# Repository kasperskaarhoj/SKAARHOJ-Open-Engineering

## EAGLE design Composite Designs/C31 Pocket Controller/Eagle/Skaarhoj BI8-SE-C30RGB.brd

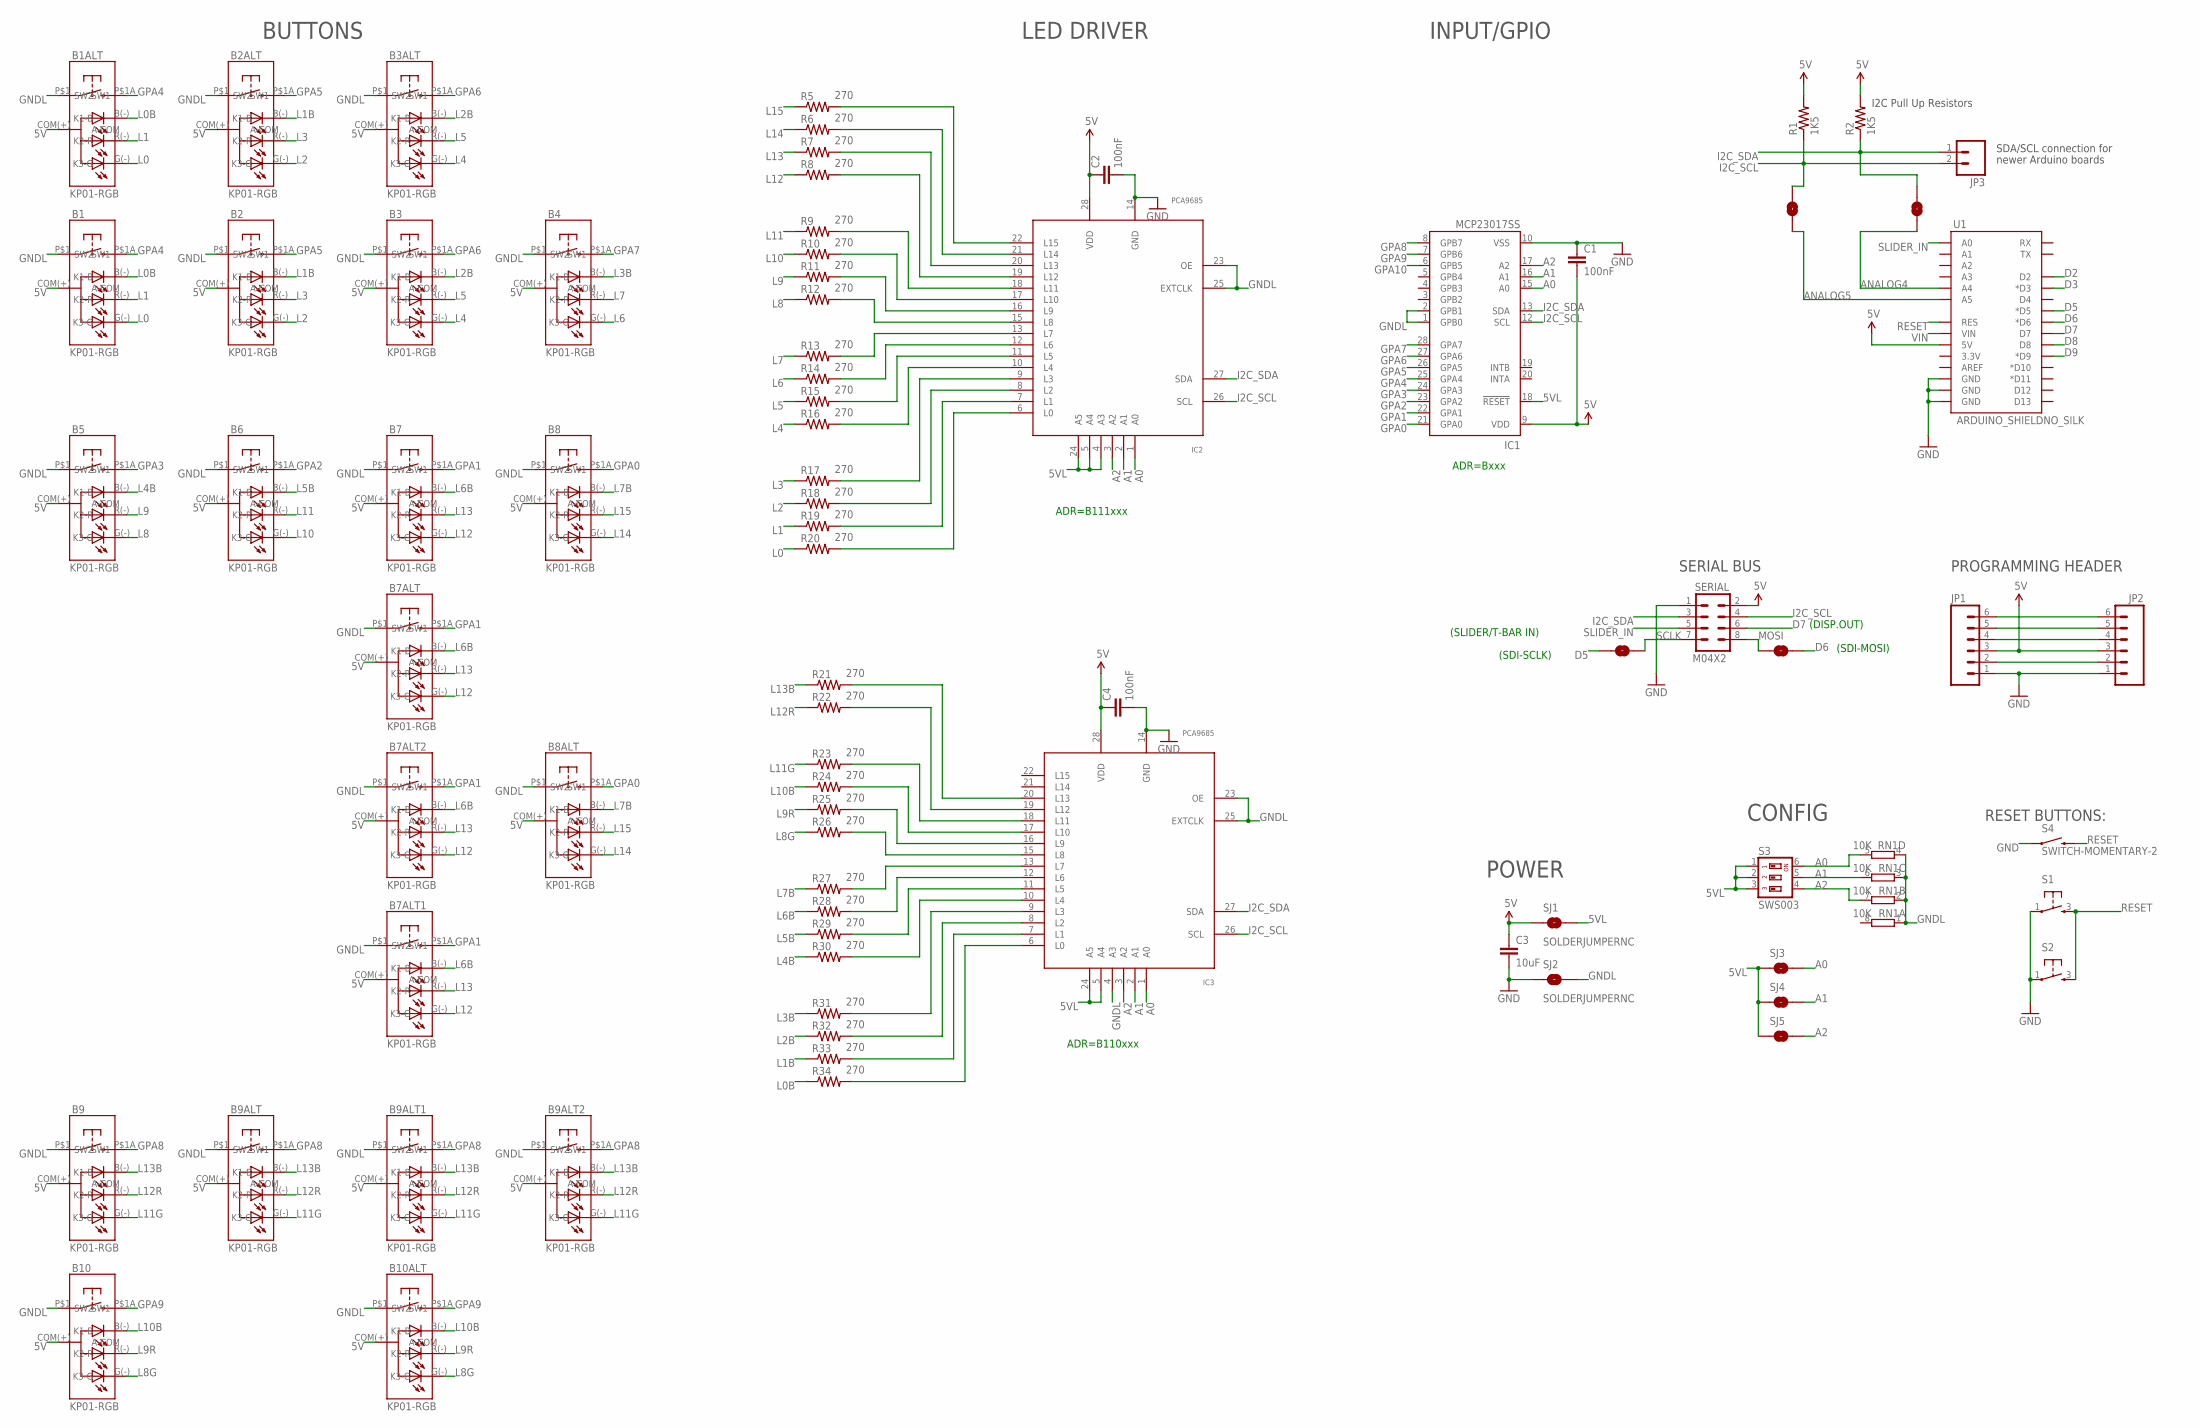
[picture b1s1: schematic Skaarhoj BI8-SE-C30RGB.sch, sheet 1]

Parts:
B1, B1ALT, B2, B2ALT, B3, B3ALT, B4, B5, B7, B8, B9, B10: KP01-RGB; NKK-KP01
B6, B7ALT, B7ALT1, B7ALT2, B8ALT, B9ALT, B9ALT1, B9ALT2, B10ALT: KP01-RGB; NKK-KP01_LESSHOLES
C1, C2, C4: 100nF; 0603-CAP
C3: 10uF; 0805
IC1: MCP23017SS; SSOP28; MPN MCP23017-E/SS
IC2, IC3: PCA9685; TSSOP28
JP1, JP2: M06POLAR; MOLEX-1X6
JP3: M02PTH; 1X02
MOSI->D6: SOLDERJUMPERNC; SJ_2S
R1, R2: 1K5; 0603-RES
R5, R6, R7, R8, R9, R10, R11, R12, R13, R14, R15, R16, R17, R18, R19, R20, R21, R22, R23, R24, R25, R26, R27, R28, R29, R30, R31, R32, R33, R34: 270; 0603-RES
RN1: 10K; CAY16_HAND
S1, S2: TAC_SWITCH; PUSHBUTTON
S3: SWS003; SMS-003
S3->A2, S3->A3: SOLDERJUMPERNC; SJ_2S
S4: SWITCH-MOMENTARY-2; TACTILE_SWITCH_TALL
SCLK->D5: SOLDERJUMPERNC; SJ_2S
SERIAL: M04X2; 2X4
SJ1, SJ2, SJ3, SJ4, SJ5: SOLDERJUMPERNC; SJ_2S
U1: ARDUINO_SHIELDNO_SILK; DUEMILANOVE_VIAS

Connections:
5V: B1.COM(+) (A-COM), B1ALT.COM(+) (A-COM), B2.COM(+) (A-COM), B2ALT.COM(+) (A-COM), B3.COM(+) (A-COM), B3ALT.COM(+) (A-COM), B4.COM(+) (A-COM), B5.COM(+) (A-COM), B6.COM(+) (A-COM), B7.COM(+) (A-COM), B7ALT.COM(+) (A-COM), B7ALT1.COM(+) (A-COM), B7ALT2.COM(+) (A-COM), B8.COM(+) (A-COM), B8ALT.COM(+) (A-COM), B9.COM(+) (A-COM), B9ALT.COM(+) (A-COM), B9ALT1.COM(+) (A-COM), B9ALT2.COM(+) (A-COM), B10.COM(+) (A-COM), B10ALT.COM(+) (A-COM), C1.2, C2.1, C3.1, C4.1, IC1.9 (VDD), IC2.28 (VDD), IC3.28 (VDD), JP1.3, JP2.3, R1.2, R2.2, SERIAL.2, SJ1.1, U1.5V
5VL: IC1.18 (!RESET), IC2.4 (A3), IC2.5 (A4), IC2.24 (A5), IC3.5 (A4), IC3.24 (A5), S3.1, S3.2, S3.3, SJ1.2, SJ3.1, SJ4.1, SJ5.1
A0: IC1.15 (A0), IC2.1 (A0), IC3.1 (A0), RN1.5 (2), S3.6, SJ3.2
A1: IC1.16 (A1), IC2.2 (A1), IC3.2 (A1), RN1.6 (2), S3.5, SJ4.2
A2: IC1.17 (A2), IC2.3 (A2), IC3.3 (A2), RN1.7 (2), S3.4, SJ5.2
ANALOG4: S3->A3.2, U1.A4
ANALOG5: S3->A2.2, U1.A5
D2: U1.D2
D3: U1.D3 (*D3)
D5: SCLK->D5.1, U1.D5 (*D5)
D6: MOSI->D6.2, U1.D6 (*D6)
D7: SERIAL.6, U1.D7
D8: U1.D8
D9: U1.D9 (*D9)
GND: C1.1, C2.2, C3.2, C4.2, IC1.10 (VSS), IC2.14 (GND), IC3.14 (GND), JP1.1, JP2.1, S1.1, S2.1, S4.A2 (1), SERIAL.1, SJ2.1, U1.GND@0 (GND), U1.GND@1 (GND), U1.GND@2 (GND)
GNDL: B1.P$1 (SW1), B1ALT.P$1 (SW1), B2.P$1 (SW1), B2ALT.P$1 (SW1), B3.P$1 (SW1), B3ALT.P$1 (SW1), B4.P$1 (SW1), B5.P$1 (SW1), B6.P$1 (SW1), B7.P$1 (SW1), B7ALT.P$1 (SW1), B7ALT1.P$1 (SW1), B7ALT2.P$1 (SW1), B8.P$1 (SW1), B8ALT.P$1 (SW1), B9.P$1 (SW1), B9ALT.P$1 (SW1), B9ALT1.P$1 (SW1), B9ALT2.P$1 (SW1), B10.P$1 (SW1), B10ALT.P$1 (SW1), IC1.1 (GPB0), IC1.2 (GPB1), IC2.23 (OE), IC2.25 (EXTCLK), IC3.4 (A3), IC3.23 (OE), IC3.25 (EXTCLK), RN1.1, RN1.2 (1), RN1.3 (1), RN1.4 (1), SJ2.2
GPA0: B8.P$1A (SW2), B8ALT.P$1A (SW2), IC1.21 (GPA0)
GPA1: B7.P$1A (SW2), B7ALT.P$1A (SW2), B7ALT1.P$1A (SW2), B7ALT2.P$1A (SW2), IC1.22 (GPA1)
GPA2: B6.P$1A (SW2), IC1.23 (GPA2)
GPA3: B5.P$1A (SW2), IC1.24 (GPA3)
GPA4: B1.P$1A (SW2), B1ALT.P$1A (SW2), IC1.25 (GPA4)
GPA5: B2.P$1A (SW2), B2ALT.P$1A (SW2), IC1.26 (GPA5)
GPA6: B3.P$1A (SW2), B3ALT.P$1A (SW2), IC1.27 (GPA6)
GPA7: B4.P$1A (SW2), IC1.28 (GPA7)
GPA8: B9.P$1A (SW2), B9ALT.P$1A (SW2), B9ALT1.P$1A (SW2), B9ALT2.P$1A (SW2), IC1.8 (GPB7)
GPA9: B10.P$1A (SW2), B10ALT.P$1A (SW2), IC1.7 (GPB6)
GPA10: IC1.6 (GPB5)
I2C_SCL: IC1.12 (SCL), IC2.26 (SCL), IC3.26 (SCL), JP3.2, R1.1, S3->A2.1, SERIAL.4
I2C_SDA: IC1.13 (SDA), IC2.27 (SDA), IC3.27 (SDA), JP3.1, R2.1, S3->A3.1, SERIAL.3
L0: B1.G(-) (K3-G), B1ALT.G(-) (K3-G), R20.1
L0B: B1.B(-) (K1-B), B1ALT.B(-) (K1-B), R34.1
L1: B1.R(-) (K2-R), B1ALT.R(-) (K2-R), R19.1
L1B: B2.B(-) (K1-B), B2ALT.B(-) (K1-B), R33.1
L2: B2.G(-) (K3-G), B2ALT.G(-) (K3-G), R18.1
L2B: B3.B(-) (K1-B), B3ALT.B(-) (K1-B), R32.1
L3: B2.R(-) (K2-R), B2ALT.R(-) (K2-R), R17.1
L3B: B4.B(-) (K1-B), R31.1
L4: B3.G(-) (K3-G), B3ALT.G(-) (K3-G), R16.1
L4B: B5.B(-) (K1-B), R30.1
L5: B3.R(-) (K2-R), B3ALT.R(-) (K2-R), R15.1
L5B: B6.B(-) (K1-B), R29.1
L6: B4.G(-) (K3-G), R14.1
L6B: B7.B(-) (K1-B), B7ALT.B(-) (K1-B), B7ALT1.B(-) (K1-B), B7ALT2.B(-) (K1-B), R28.1
L7: B4.R(-) (K2-R), R13.1
L7B: B8.B(-) (K1-B), B8ALT.B(-) (K1-B), R27.1
L8: B5.G(-) (K3-G), R12.1
L8G: B10.G(-) (K3-G), B10ALT.G(-) (K3-G), R26.1
L9: B5.R(-) (K2-R), R11.1
L9R: B10.R(-) (K2-R), B10ALT.R(-) (K2-R), R25.1
L10: B6.G(-) (K3-G), R10.1
L10B: B10.B(-) (K1-B), B10ALT.B(-) (K1-B), R24.1
L11: B6.R(-) (K2-R), R9.1
L11G: B9.G(-) (K3-G), B9ALT.G(-) (K3-G), B9ALT1.G(-) (K3-G), B9ALT2.G(-) (K3-G), R23.1
L12: B7.G(-) (K3-G), B7ALT.G(-) (K3-G), B7ALT1.G(-) (K3-G), B7ALT2.G(-) (K3-G), R8.1
L12R: B9.R(-) (K2-R), B9ALT.R(-) (K2-R), B9ALT1.R(-) (K2-R), B9ALT2.R(-) (K2-R), R22.1
L13: B7.R(-) (K2-R), B7ALT.R(-) (K2-R), B7ALT1.R(-) (K2-R), B7ALT2.R(-) (K2-R), R7.1
L13B: B9.B(-) (K1-B), B9ALT.B(-) (K1-B), B9ALT1.B(-) (K1-B), B9ALT2.B(-) (K1-B), R21.1
L14: B8.G(-) (K3-G), B8ALT.G(-) (K3-G), R6.1
L15: B8.R(-) (K2-R), B8ALT.R(-) (K2-R), R5.1
MOSI: MOSI->D6.1, SERIAL.8
unnamed: JP1.2, JP2.2
unnamed: IC3.13 (L7), R27.2
unnamed: IC3.12 (L6), R28.2
unnamed: IC2.13 (L7), R13.2
unnamed: IC2.12 (L6), R14.2
unnamed: IC3.11 (L5), R29.2
unnamed: IC2.11 (L5), R15.2
unnamed: IC2.10 (L4), R16.2
unnamed: IC2.9 (L3), R17.2
unnamed: IC2.8 (L2), R18.2
unnamed: IC2.7 (L1), R19.2
unnamed: IC3.10 (L4), R30.2
unnamed: IC3.9 (L3), R31.2
unnamed: IC3.8 (L2), R32.2
unnamed: IC3.7 (L1), R33.2
unnamed: IC3.6 (L0), R34.2
unnamed: IC3.15 (L8), R26.2
unnamed: IC2.6 (L0), R20.2
unnamed: IC2.15 (L8), R12.2
unnamed: IC2.16 (L9), R11.2
unnamed: IC2.17 (L10), R10.2
unnamed: IC2.18 (L11), R9.2
unnamed: IC2.19 (L12), R8.2
unnamed: IC2.20 (L13), R7.2
unnamed: IC2.21 (L14), R6.2
unnamed: IC2.22 (L15), R5.2
unnamed: IC3.16 (L9), R25.2
unnamed: IC3.17 (L10), R24.2
unnamed: IC3.18 (L11), R23.2
unnamed: IC3.19 (L12), R22.2
unnamed: IC3.20 (L13), R21.2
unnamed: JP1.4, JP2.4
unnamed: JP1.5, JP2.5
unnamed: JP1.6, JP2.6
RESET: S1.3, S2.3, S4.B2 (2), U1.RES
SCLK: SCLK->D5.2, SERIAL.7
SLIDER_IN: SERIAL.5, U1.A0
VIN: U1.VIN

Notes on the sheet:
PROGRAMMING HEADER
I2C Pull Up Resistors
SDA/SCL connection for
newer Arduino boards
SERIAL BUS
(SLIDER/T-BAR IN)
(SDI-SCLK)
(SDI-MOSI)
(DISP.OUT)
RESET BUTTONS:
ADR=B111xxx
ADR=Bxxx
BUTTONS
LED DRIVER
INPUT/GPIO
POWER
CONFIG
ADR=B110xxx

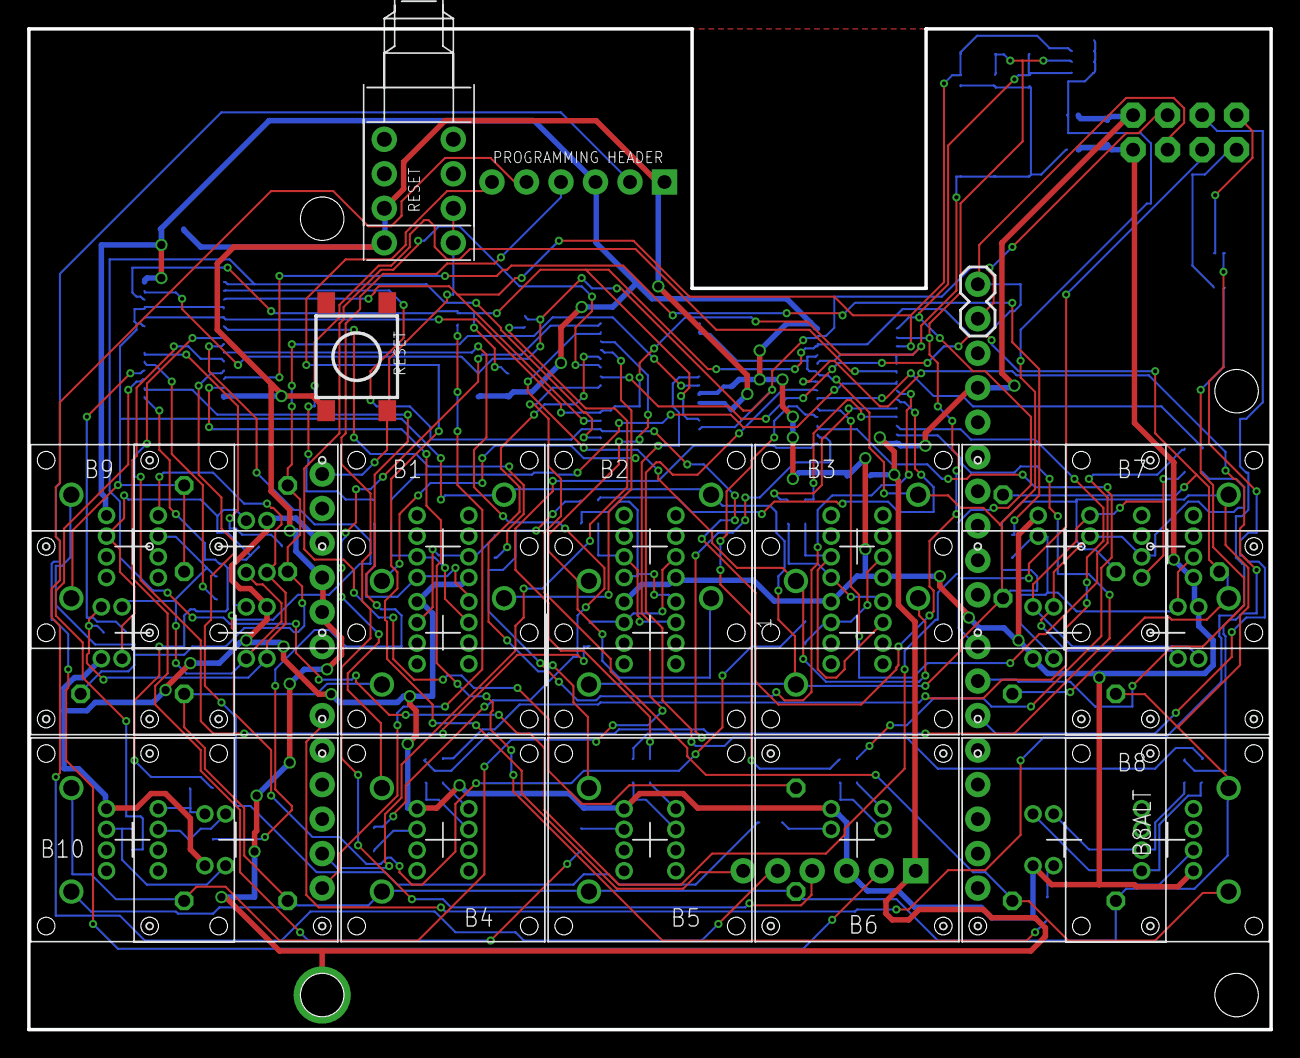
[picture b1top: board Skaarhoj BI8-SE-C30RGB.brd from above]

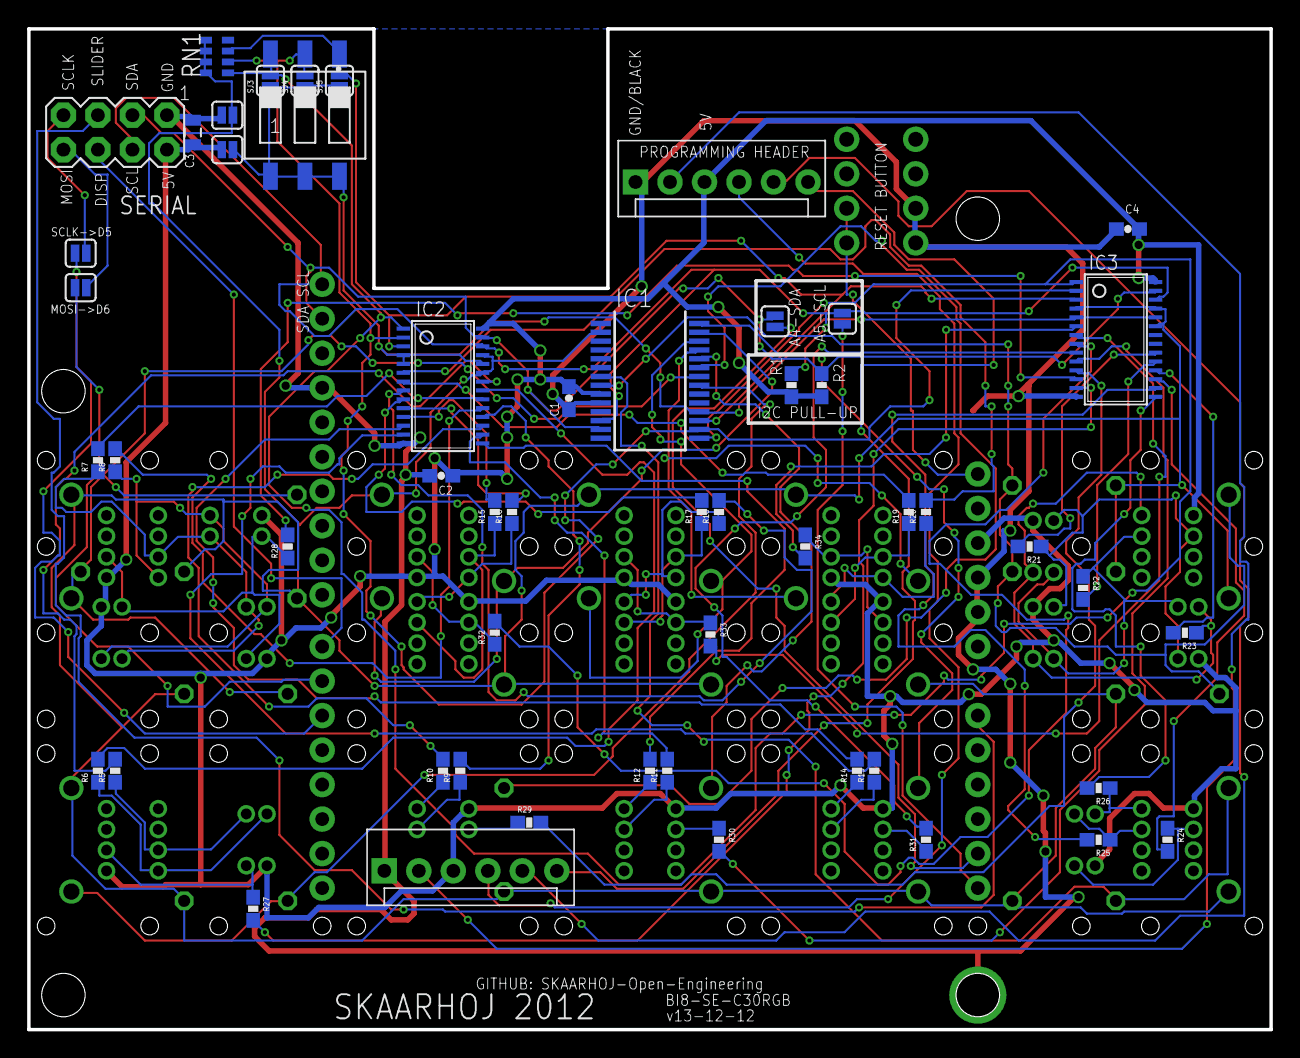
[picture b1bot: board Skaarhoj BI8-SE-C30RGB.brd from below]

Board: 2 copper layers, 91.4 x 73.7 mm, 79 parts (53 on the bottom side), 92 nets.

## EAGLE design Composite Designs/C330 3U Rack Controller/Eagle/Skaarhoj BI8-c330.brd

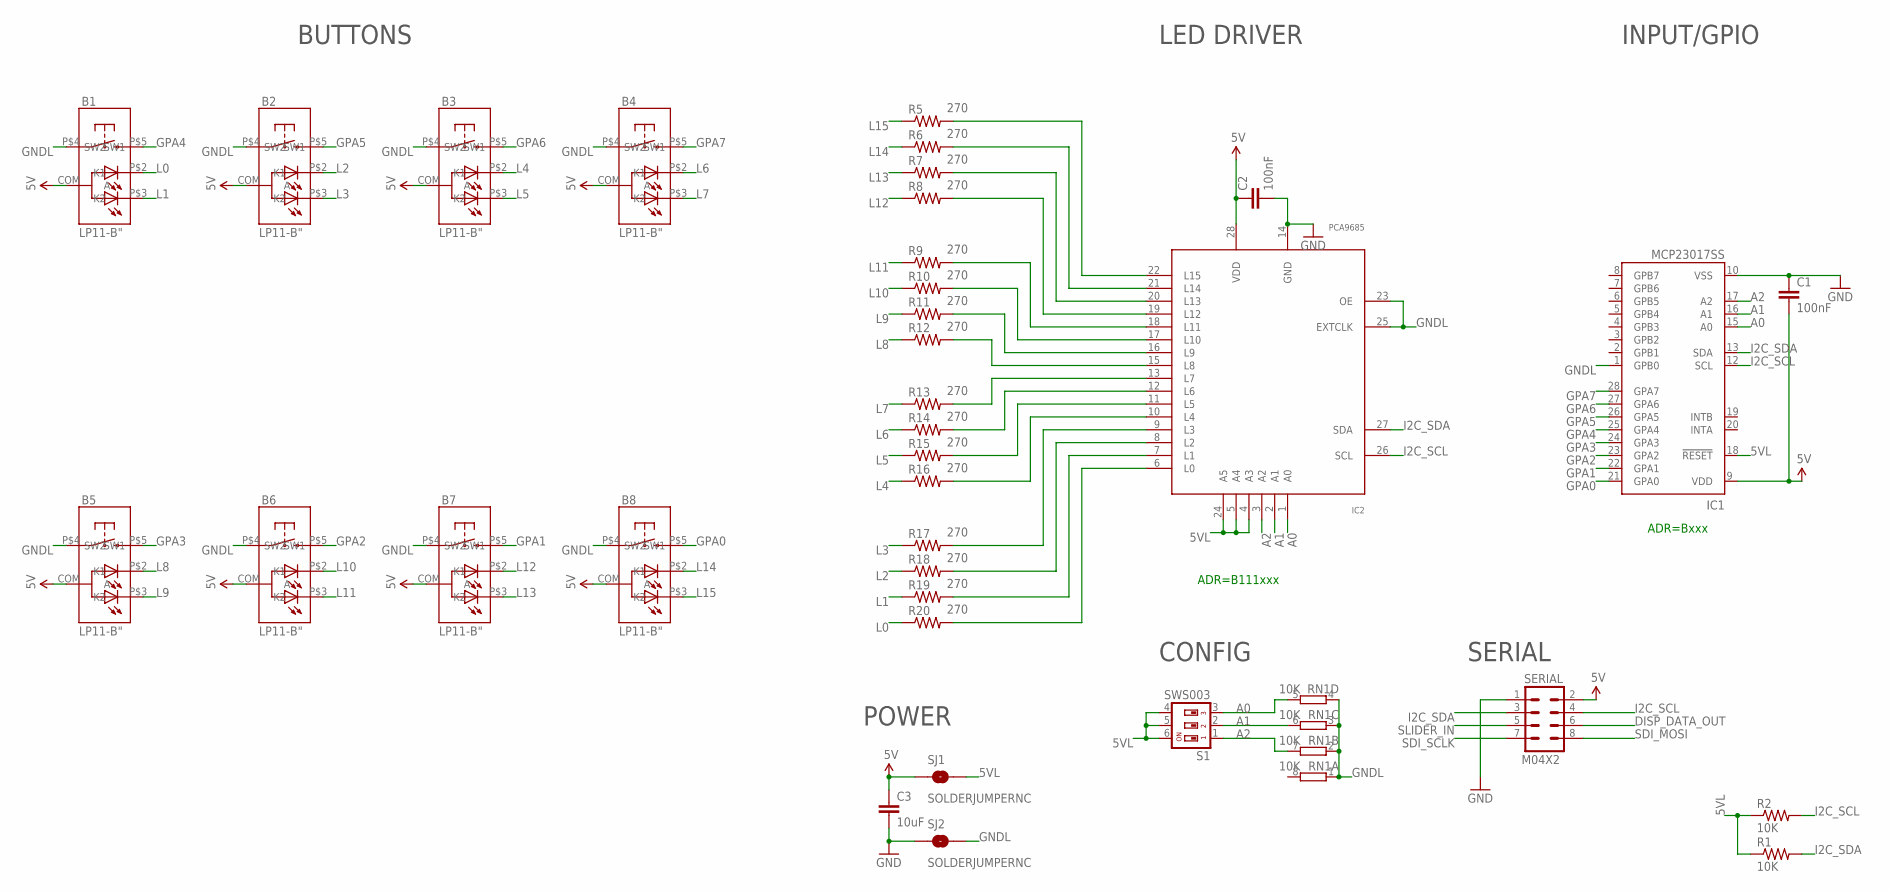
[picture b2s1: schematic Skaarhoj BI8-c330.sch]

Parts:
B1, B2, B3, B4, B5, B6, B7, B8: LP11-B"; LP11
C1, C2: 100nF; 0603-CAP
C3: 10uF; 0805
IC1: MCP23017SS; SSOP28; MPN MCP23017-E/SS
IC2: PCA9685; TSSOP28
R1, R2: 10K; 0603-RES
R5, R6, R7, R8, R9, R10, R11, R12, R13, R14, R15, R16, R17, R18, R19, R20: 270; 0603-RES
RN1: 10K; CAY16_HAND
S1: SWS003; SMS-003
SERIAL: M04X2; 2X4
SJ1, SJ2: SOLDERJUMPERNC; SJ_2S

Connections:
5V: B1.COM (A), B2.COM (A), B3.COM (A), B4.COM (A), B5.COM (A), B6.COM (A), B7.COM (A), B8.COM (A), C1.2, C2.1, C3.1, IC1.9 (VDD), IC2.28 (VDD), SERIAL.2, SJ1.1
5VL: IC1.18 (!RESET), IC2.4 (A3), IC2.5 (A4), IC2.24 (A5), R1.1, R2.1, S1.4, S1.5, S1.6, SJ1.2
A0: IC1.15 (A0), IC2.1 (A0), RN1.5 (2), S1.3
A1: IC1.16 (A1), IC2.2 (A1), RN1.6 (2), S1.2
A2: IC1.17 (A2), IC2.3 (A2), RN1.7 (2), S1.1
DISP_DATA_OUT: SERIAL.6
GND: C1.1, C2.2, C3.2, IC1.10 (VSS), IC2.14 (GND), SERIAL.1, SJ2.1
GNDL: B1.P$4 (SW1), B2.P$4 (SW1), B3.P$4 (SW1), B4.P$4 (SW1), B5.P$4 (SW1), B6.P$4 (SW1), B7.P$4 (SW1), B8.P$4 (SW1), IC1.1 (GPB0), IC2.23 (OE), IC2.25 (EXTCLK), RN1.1, RN1.2 (1), RN1.3 (1), RN1.4 (1), SJ2.2
GPA0: B8.P$5 (SW2), IC1.21 (GPA0)
GPA1: B7.P$5 (SW2), IC1.22 (GPA1)
GPA2: B6.P$5 (SW2), IC1.23 (GPA2)
GPA3: B5.P$5 (SW2), IC1.24 (GPA3)
GPA4: B1.P$5 (SW2), IC1.25 (GPA4)
GPA5: B2.P$5 (SW2), IC1.26 (GPA5)
GPA6: B3.P$5 (SW2), IC1.27 (GPA6)
GPA7: B4.P$5 (SW2), IC1.28 (GPA7)
I2C_SCL: IC1.12 (SCL), IC2.26 (SCL), R2.2, SERIAL.4
I2C_SDA: IC1.13 (SDA), IC2.27 (SDA), R1.2, SERIAL.3
L0: B1.P$2 (K1), R20.1
L1: B1.P$3 (K2), R19.1
L2: B2.P$2 (K1), R18.1
L3: B2.P$3 (K2), R17.1
L4: B3.P$2 (K1), R16.1
L5: B3.P$3 (K2), R15.1
L6: B4.P$2 (K1), R14.1
L7: B4.P$3 (K2), R13.1
L8: B5.P$2 (K1), R12.1
L9: B5.P$3 (K2), R11.1
L10: B6.P$2 (K1), R10.1
L11: B6.P$3 (K2), R9.1
L12: B7.P$2 (K1), R8.1
L13: B7.P$3 (K2), R7.1
L14: B8.P$2 (K1), R6.1
L15: B8.P$3 (K2), R5.1
unnamed: IC2.13 (L7), R13.2
unnamed: IC2.12 (L6), R14.2
unnamed: IC2.11 (L5), R15.2
unnamed: IC2.10 (L4), R16.2
unnamed: IC2.9 (L3), R17.2
unnamed: IC2.8 (L2), R18.2
unnamed: IC2.7 (L1), R19.2
unnamed: IC2.6 (L0), R20.2
unnamed: IC2.15 (L8), R12.2
unnamed: IC2.16 (L9), R11.2
unnamed: IC2.17 (L10), R10.2
unnamed: IC2.18 (L11), R9.2
unnamed: IC2.19 (L12), R8.2
unnamed: IC2.20 (L13), R7.2
unnamed: IC2.21 (L14), R6.2
unnamed: IC2.22 (L15), R5.2
SDI_MOSI: SERIAL.8
SDI_SCLK: SERIAL.7
SLIDER_IN: SERIAL.5

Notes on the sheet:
ADR=B111xxx
ADR=Bxxx
BUTTONS
LED DRIVER
INPUT/GPIO
POWER
CONFIG
SERIAL

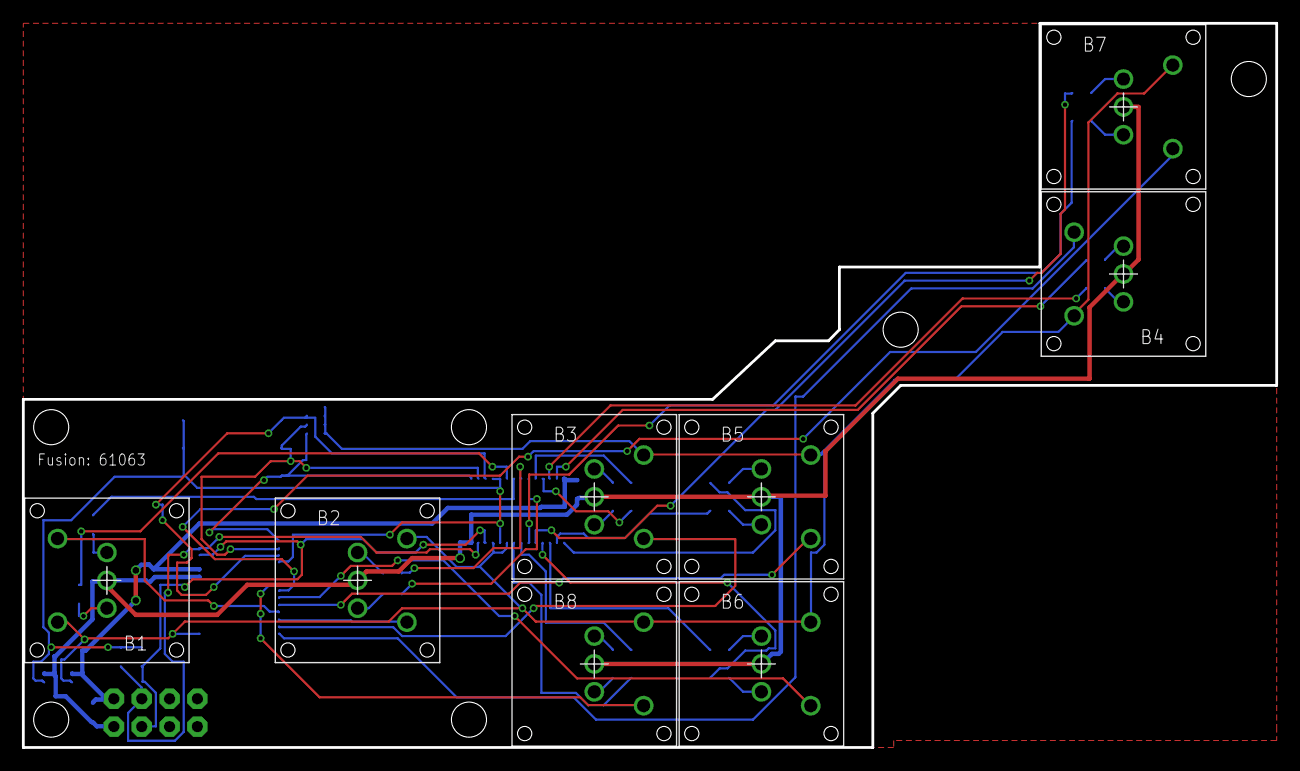
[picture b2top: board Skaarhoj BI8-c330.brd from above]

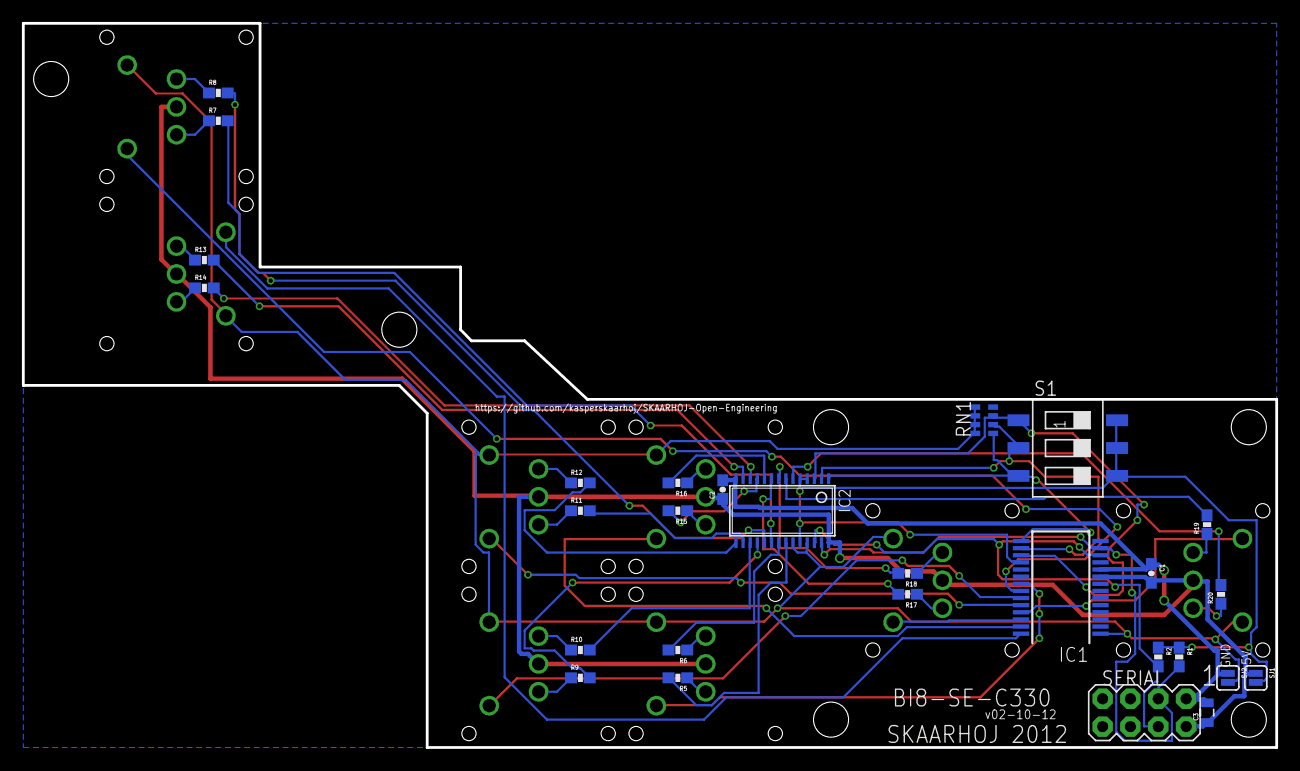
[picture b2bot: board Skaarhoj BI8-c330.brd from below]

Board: 2 copper layers, 114.3 x 66.0 mm, 36 parts (28 on the bottom side), 49 nets.

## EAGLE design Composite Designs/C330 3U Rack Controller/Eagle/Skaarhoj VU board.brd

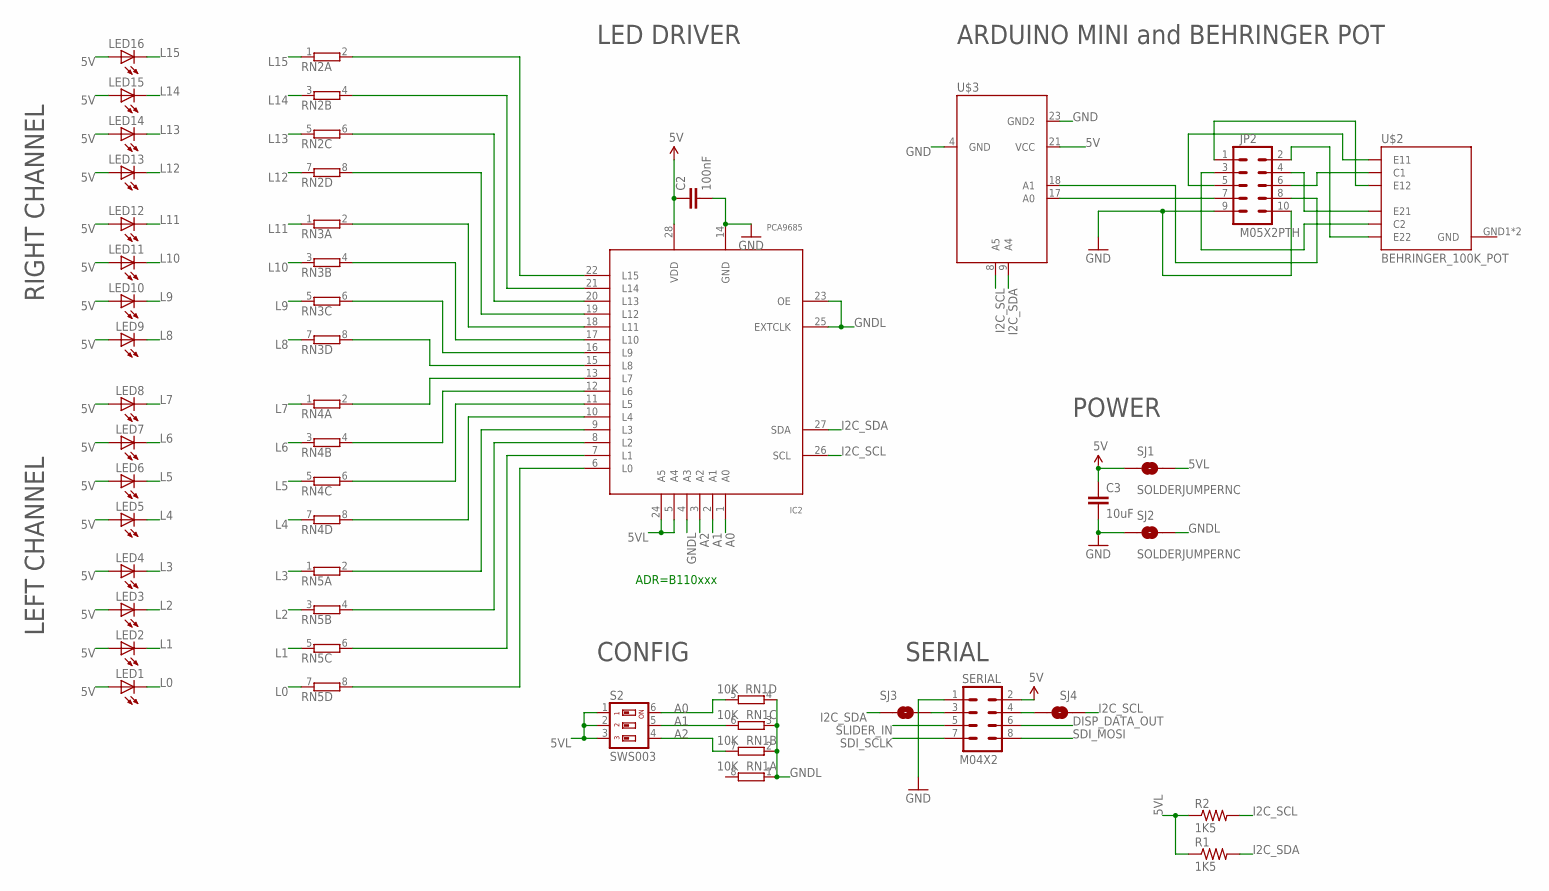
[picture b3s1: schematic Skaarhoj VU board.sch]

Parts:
C2: 100nF; 0603-CAP
C3: 10uF; 0805
IC2: PCA9685; TSSOP28
JP2: M05X2PTH; AVR_ICSP
LED1, LED2, LED3, LED4, LED5, LED6, LED7, LED8, LED9, LED10, LED11, LED12, LED13, LED14, LED15, LED16: LED3MM
R1, R2: 1K5; 0603-RES
RN1: 10K; CAY16_HAND
RN2, RN3, RN4, RN5: E4R; SIL8
S2: SWS003; SMS-003
SERIAL: M04X2; 2X4
SJ1, SJ2, SJ3, SJ4: SOLDERJUMPERNC; SJ_2S
U$2: BEHRINGER_100K_POT
U$3: ARDUINO_MINI_SE1

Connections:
5V: C2.1, C3.1, IC2.28 (VDD), LED1.A, LED2.A, LED3.A, LED4.A, LED5.A, LED6.A, LED7.A, LED8.A, LED9.A, LED10.A, LED11.A, LED12.A, LED13.A, LED14.A, LED15.A, LED16.A, SERIAL.2, SJ1.1, U$3.21 (VCC); also elsewhere on the board
A0: IC2.1 (A0), RN1.5 (2), S2.6
A1: IC2.2 (A1), RN1.6 (2), S2.5
A2: IC2.3 (A2), RN1.7 (2), S2.4
DISP_DATA_OUT: SERIAL.6
GND: C2.2, C3.2, IC2.14 (GND), JP2.9, JP2.10, SERIAL.1, SJ2.1, U$2.GND1 (GND), U$2.GND2 (GND), U$3.4 (GND), U$3.23 (GND2); also elsewhere on the board
I2C_SCL: IC2.26 (SCL), R2.2, SJ4.2, U$3.8 (A5)
I2C_SDA: IC2.27 (SDA), R1.2, SJ3.1, U$3.9 (A4)
L0: LED1.K (C), RN5.7 (1)
L1: LED2.K (C), RN5.5 (1)
L2: LED3.K (C), RN5.3 (1)
L3: LED4.K (C), RN5.1
L4: LED5.K (C), RN4.7 (1)
L5: LED6.K (C), RN4.5 (1)
L6: LED7.K (C), RN4.3 (1)
L7: LED8.K (C), RN4.1
L8: LED9.K (C), RN3.7 (1)
L9: LED10.K (C), RN3.5 (1)
L10: LED11.K (C), RN3.3 (1)
L11: LED12.K (C), RN3.1
L12: LED13.K (C), RN2.7 (1)
L13: LED14.K (C), RN2.5 (1)
L14: LED15.K (C), RN2.3 (1)
L15: LED16.K (C), RN2.1
unnamed: JP2.6, U$2.PAD1 (C1)
unnamed: JP2.4, U$2.PAD3 (E21)
unnamed: SERIAL.3, SJ3.2
unnamed: IC2.13 (L7), RN4.2
unnamed: IC2.12 (L6), RN4.4 (2)
unnamed: SERIAL.4, SJ4.1
unnamed: IC2.11 (L5), RN4.6 (2)
unnamed: JP2.3, U$2.PAD4 (C2)
unnamed: IC2.10 (L4), RN4.8 (2)
unnamed: IC2.9 (L3), RN5.2
unnamed: IC2.8 (L2), RN5.4 (2)
unnamed: IC2.7 (L1), RN5.6 (2)
unnamed: JP2.2, U$2.PAD5 (E22)
unnamed: JP2.5, U$2.PAD2 (E11)
unnamed: JP2.1, U$2.PAD6 (E12)
unnamed: JP2.8, U$3.18 (A1)
unnamed: JP2.7, U$3.17 (A0)
unnamed: IC2.6 (L0), RN5.8 (2)
unnamed: IC2.15 (L8), RN3.8 (2)
unnamed: IC2.16 (L9), RN3.6 (2)
unnamed: IC2.17 (L10), RN3.4 (2)
unnamed: IC2.18 (L11), RN3.2
unnamed: IC2.19 (L12), RN2.8 (2)
unnamed: IC2.20 (L13), RN2.6 (2)
unnamed: IC2.21 (L14), RN2.4 (2)
unnamed: IC2.22 (L15), RN2.2
unnamed 53: U$3.1; also elsewhere on the board
RX: U$3.5; also elsewhere on the board
SDI_MOSI: SERIAL.8
SDI_SCLK: SERIAL.7
SLIDER_IN: SERIAL.5
TX: U$3.6; also elsewhere on the board

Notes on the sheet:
ADR=B110xxx
LED DRIVER
POWER
CONFIG
SERIAL
ARDUINO MINI and BEHRINGER POT
LEFT CHANNEL
RIGHT CHANNEL

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
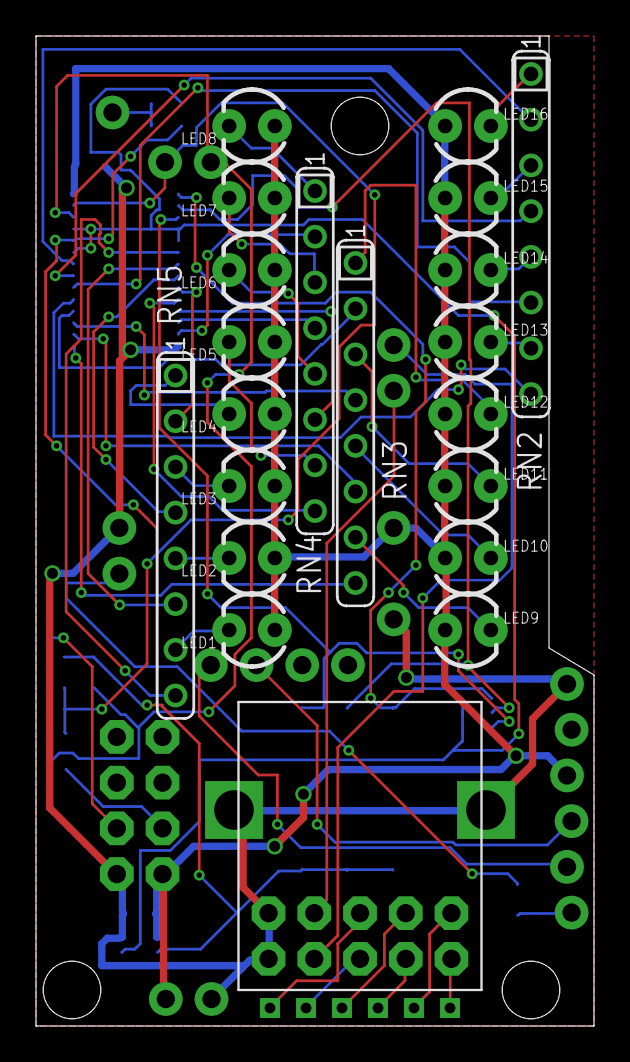
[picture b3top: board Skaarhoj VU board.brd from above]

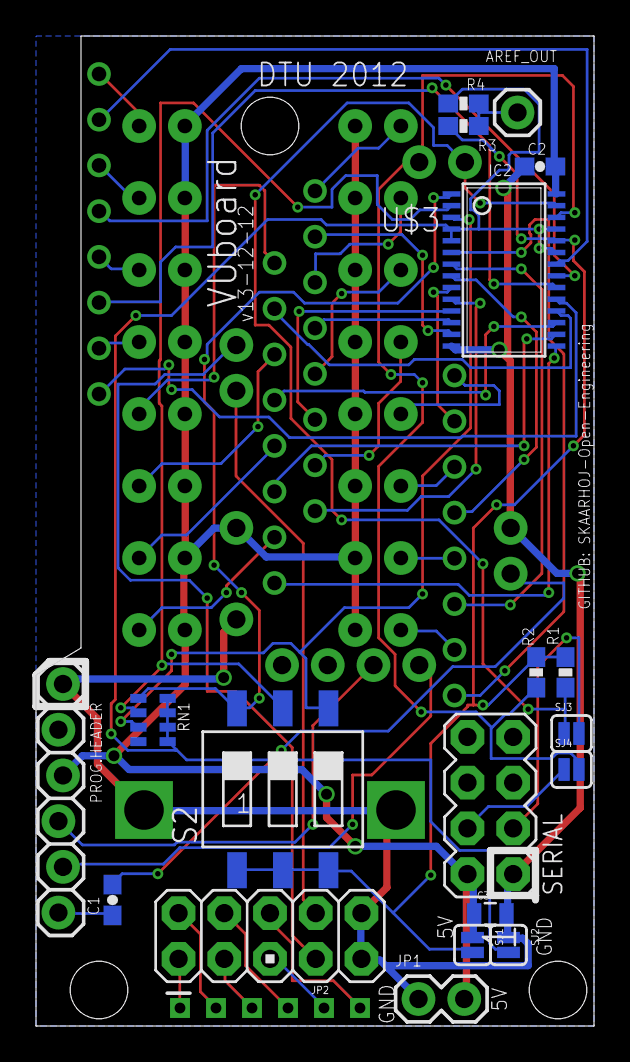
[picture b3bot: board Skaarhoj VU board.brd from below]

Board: 2 copper layers, 31.0 x 55.0 mm, 41 parts (20 on the bottom side), 56 nets.

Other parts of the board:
AREF_OUT: M01PTH; 1X01
C1: 100nF; 0603-CAP
JP1: 1X02
PROG.HEADER: 1X06_LOCK
R3, R4: 0603-RES

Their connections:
5V: JP1.2, PROG.HEADER.3; also elsewhere on the board
AREF: AREF_OUT.1, R3.1, R4.2
GND: JP1.1, PROG.HEADER.1; also elsewhere on the board
unnamed 53: C1.2; also elsewhere on the board
PH6: C1.1, PROG.HEADER.6
RX: PROG.HEADER.4; also elsewhere on the board
TX: PROG.HEADER.5; also elsewhere on the board

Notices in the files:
parts and their libraries:
SparkFun: Licensing: CC v3.0 Share-Alike You are welcome to use this library for commercial purposes.
